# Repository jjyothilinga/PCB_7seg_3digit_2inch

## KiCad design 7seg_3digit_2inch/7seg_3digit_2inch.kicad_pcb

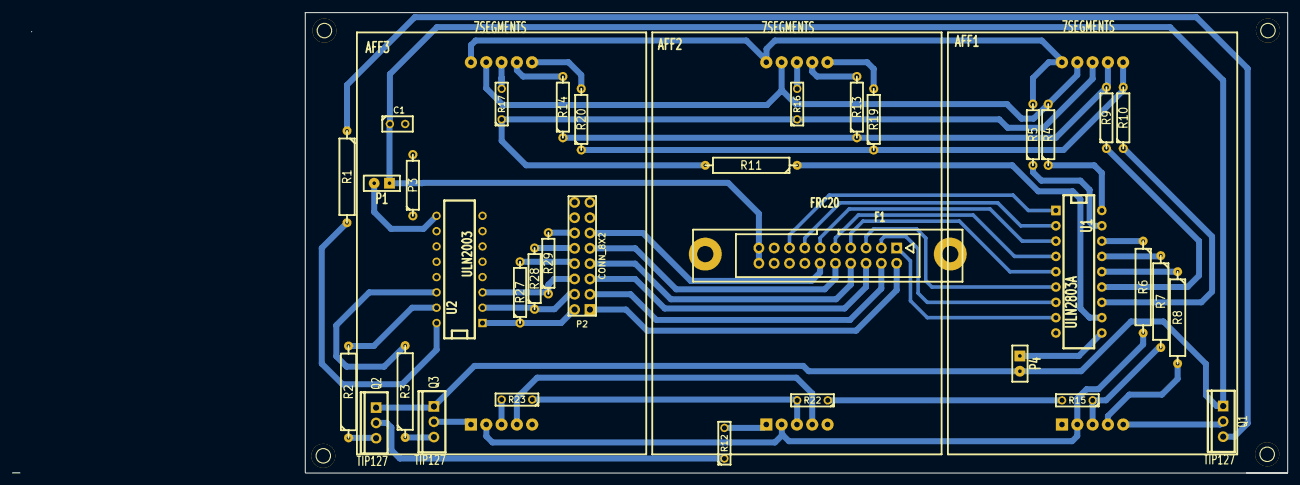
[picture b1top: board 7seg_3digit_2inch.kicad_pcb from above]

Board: 2 copper layers, 211.6 x 76.4 mm, 38 parts (0 on the bottom side), 59 nets.

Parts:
AFF1, AFF2, AFF3: 7SEGMENTS; 2INCH_DISPLAY_REVERSE_PINS
C1: C; C1
F1: FRC20; HE10_20D
P1, P4: CONN_2; Ideonics_RMC_2
P2: CONN_8X2; pin_array_8x2
P3: GND_JMP; R4
Q1, Q2, Q3: TIP127; TO220_VERT
R1, R2, R3: 2.2K; Ideonics_R
R4, R5, R9, R10: 820; R4
R6, R7, R8, R11: 820; Ideonics_R
R12: JMP; C2
R13, R14: JMP_F; R4
R15, R22, R23: JMP_D; C2
R16, R17: JMP_H; C2
R19, R20: JMP_G; R4
R27, R28, R29: JMP; R4
U1: ULN2803A; DIP-18__300
U2: ULN2003; DIP-16__300

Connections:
/D1: P2.2, R27.1, U2.1
/D1_JMP: P2.8, R27.2
/D2: P2.4, R28.1, U2.2
/D2_JMP: P2.10, R28.2
/D3: P2.6, R29.1, U2.3
/D3_JMP: P2.12, R29.2
/DIG_1: AFF1.1, Q1.2
/DIG_2: Q2.2, R12.1
/DIG_2_JMP: AFF2.5, R12.2
/DIG_3: AFF3.5, Q3.2
/IA: F1.15, U1.1
/IB: F1.13, U1.2
/IC: F1.11, U1.3
/ID: F1.9, U1.4
/IE: F1.7, U1.5
/IF: F1.5, U1.6
/IG: F1.3, U1.7
/IH: F1.1, U1.8
/SEG_A: AFF1.7, AFF2.7, AFF3.7, R4.2
/SEG_B: AFF1.6, AFF2.6, AFF3.6, R5.2
/SEG_C: AFF1.4, AFF2.4, AFF3.4, R6.2
/SEG_D: AFF1.3, R7.2, R15.1
/SEG_D1: R15.2, R22.1
/SEG_D2: AFF2.3, R22.2, R23.1
/SEG_D3: AFF3.3, R23.2
/SEG_E: AFF1.2, AFF2.2, AFF3.2, R8.2
/SEG_F: AFF1.9, R9.2, R13.1, R14.1
/SEG_F2: AFF2.9, R13.2
/SEG_F3: AFF3.9, R14.2
/SEG_G: AFF1.10, R10.2, R19.1, R20.1
/SEG_G2: AFF2.10, R19.2
/SEG_G3: AFF3.10, R20.2
/SEG_H: AFF1.8, R11.2, R16.1, R17.1
/SEG_H2: AFF2.8, R16.2
/SEG_H3: AFF3.8, R17.2
/VCC: C1.1, F1.19, F1.20, P1.1, P4.2, Q1.3, Q2.3, Q3.3
GND: C1.2, F1.17, F1.18, P3.1, P3.2, U1.9, U2.8
unnamed: R2.2, U2.15
unnamed: F1.12, P2.11
unnamed: F1.10, P2.9
unnamed: F1.8, P2.7
unnamed: F1.6, P2.5
unnamed: F1.4, P2.3
unnamed: F1.2, P2.1
unnamed: R3.2, U2.14
unnamed: R1.2, U2.16
unnamed: Q2.1, R2.1
unnamed: Q1.1, R1.1
unnamed: P4.1, U1.10
unnamed: R5.1, U1.17
unnamed: R4.1, U1.18
unnamed: R6.1, U1.16
unnamed: P1.2, U2.9
unnamed: Q3.1, R3.1
unnamed: R11.1, U1.11
unnamed: R10.1, U1.12
unnamed: R9.1, U1.13
unnamed: R8.1, U1.14
unnamed: R7.1, U1.15

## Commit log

2015-05-30 :neckbeard: Added .gitattributes & .gitignore files
2015-05-30 Project Creation
